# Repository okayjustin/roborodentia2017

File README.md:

# roborodentia2017

To rebuild the newlib libraries (embedded standard C libs):

	cd [REPOSITORY TOP LEVEL DIRECTORY]
	mkdir newlib_arm-none-eabi              					// Or whatever folder name you like
	cd newlib_arm-none-eabi
	../newlib-cygwin/configure
         --target=arm-none-eabi \
         --with-cpu=cortex-m4 \
         --with-fpu=fpv4-sp-d16 \
         --with-float=hard \
         --with-mode=thumb \
         --enable-interwork \        // Not sure if you need this one
         --enable-multilib \         // Not sure if you need this one
         --with-gnu-as \
         --with-gnu-ld \
         --disable-nls \
         --disable-newlib-supplied-syscalls  // Or whatever version of newlib source you have
    sudo make -j4 all

Then take the libc.a and libm.a from newlib_arm-none-eabi/arm-none-eabi/newlib and place them in buildTools.
Also take libnosys.a from newlib_arm-none-eabi/arm-none-eabi/thumb/libgloss/libnosys and place it in buildTools.

Then take the libc.a and libm.a from newlib_arm-none-eabi/arm-none-eabi/fpu/newlib and place them in buildTools.
Also take libnosys.a from newlib_arm-none-eabi/arm-none-eabi/fpu/libgloss/libnosys and place it in buildTools.

Debugging tips:

    > openocd -f firmware/buildTools/st_nucleo_f4.cfg
    > arm-none-eabi-gdb firmware/build/program.elf
    (gdb) target remote localhost:3333
    (gdb) monitor reset halt
    (gdb) b main.c:50
    (gdb) p data[0]
    (gdb) x/1hx 0x40005400

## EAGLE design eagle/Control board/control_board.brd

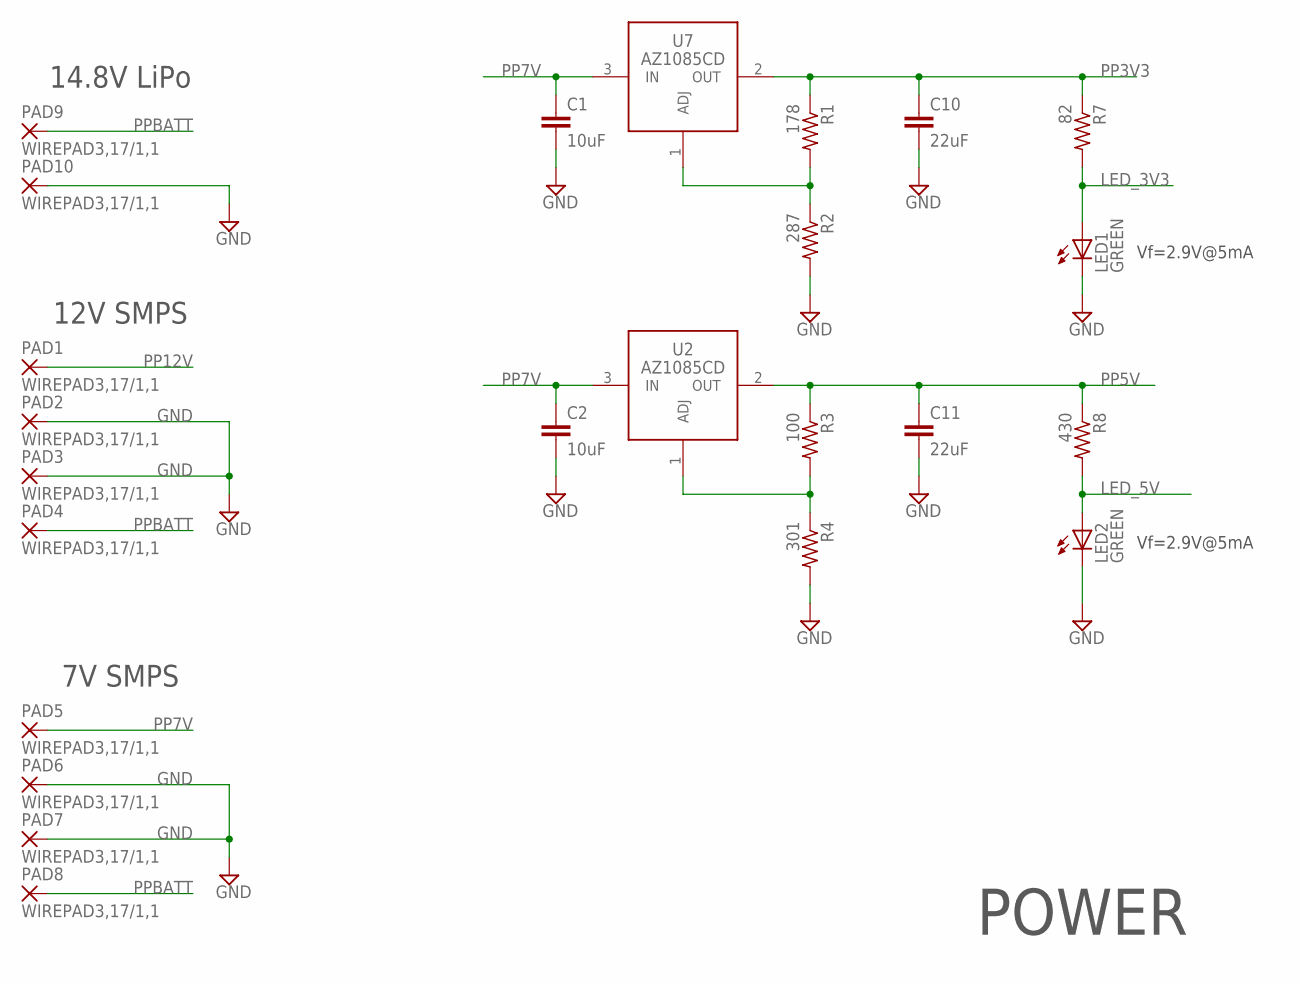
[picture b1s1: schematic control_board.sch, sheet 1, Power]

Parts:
C1, C2: 10uF; C0603
C10, C11: 22uF; C0603
LED1, LED2: GREEN; CHIPLED_0805; DIGI 732-4971-1-ND
PAD1, PAD2, PAD3, PAD4, PAD5, PAD6, PAD7, PAD8, PAD9, PAD10: WIREPAD3,17/1,1; 3,17/1,1
R1: 178; R0603
R2: 287; R0603
R3: 100; R0603
R4: 301; R0603
R7: 82; R0603
R8: 430; R0603
U2, U7: AZ1085CD; TO252

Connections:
GND: C1.2, C2.2, C10.2, C11.2, LED1.C, LED2.C, PAD2.1, PAD3.1, PAD6.1, PAD7.1, PAD10.1, R2.2, R4.2; also elsewhere on the board
LED_3V3: LED1.A, R7.2
LED_5V: LED2.A, R8.2
unnamed: R3.2, R4.1, U2.1 (ADJ)
unnamed: R1.2, R2.1, U7.1 (ADJ)
PP3V3: C10.1, R1.1, R7.1, U7.2 (OUT); also elsewhere on the board
PP5V: C11.1, R3.1, R8.1, U2.2 (OUT); also elsewhere on the board
PP7V: C1.1, C2.1, PAD5.1, U2.3 (IN), U7.3 (IN); also elsewhere on the board
PP12V: PAD1.1; also elsewhere on the board
PPBATT: PAD4.1, PAD8.1, PAD9.1

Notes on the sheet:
14.8V LiPo
12V SMPS
7V SMPS
Vf=2.9V@5mA
POWER

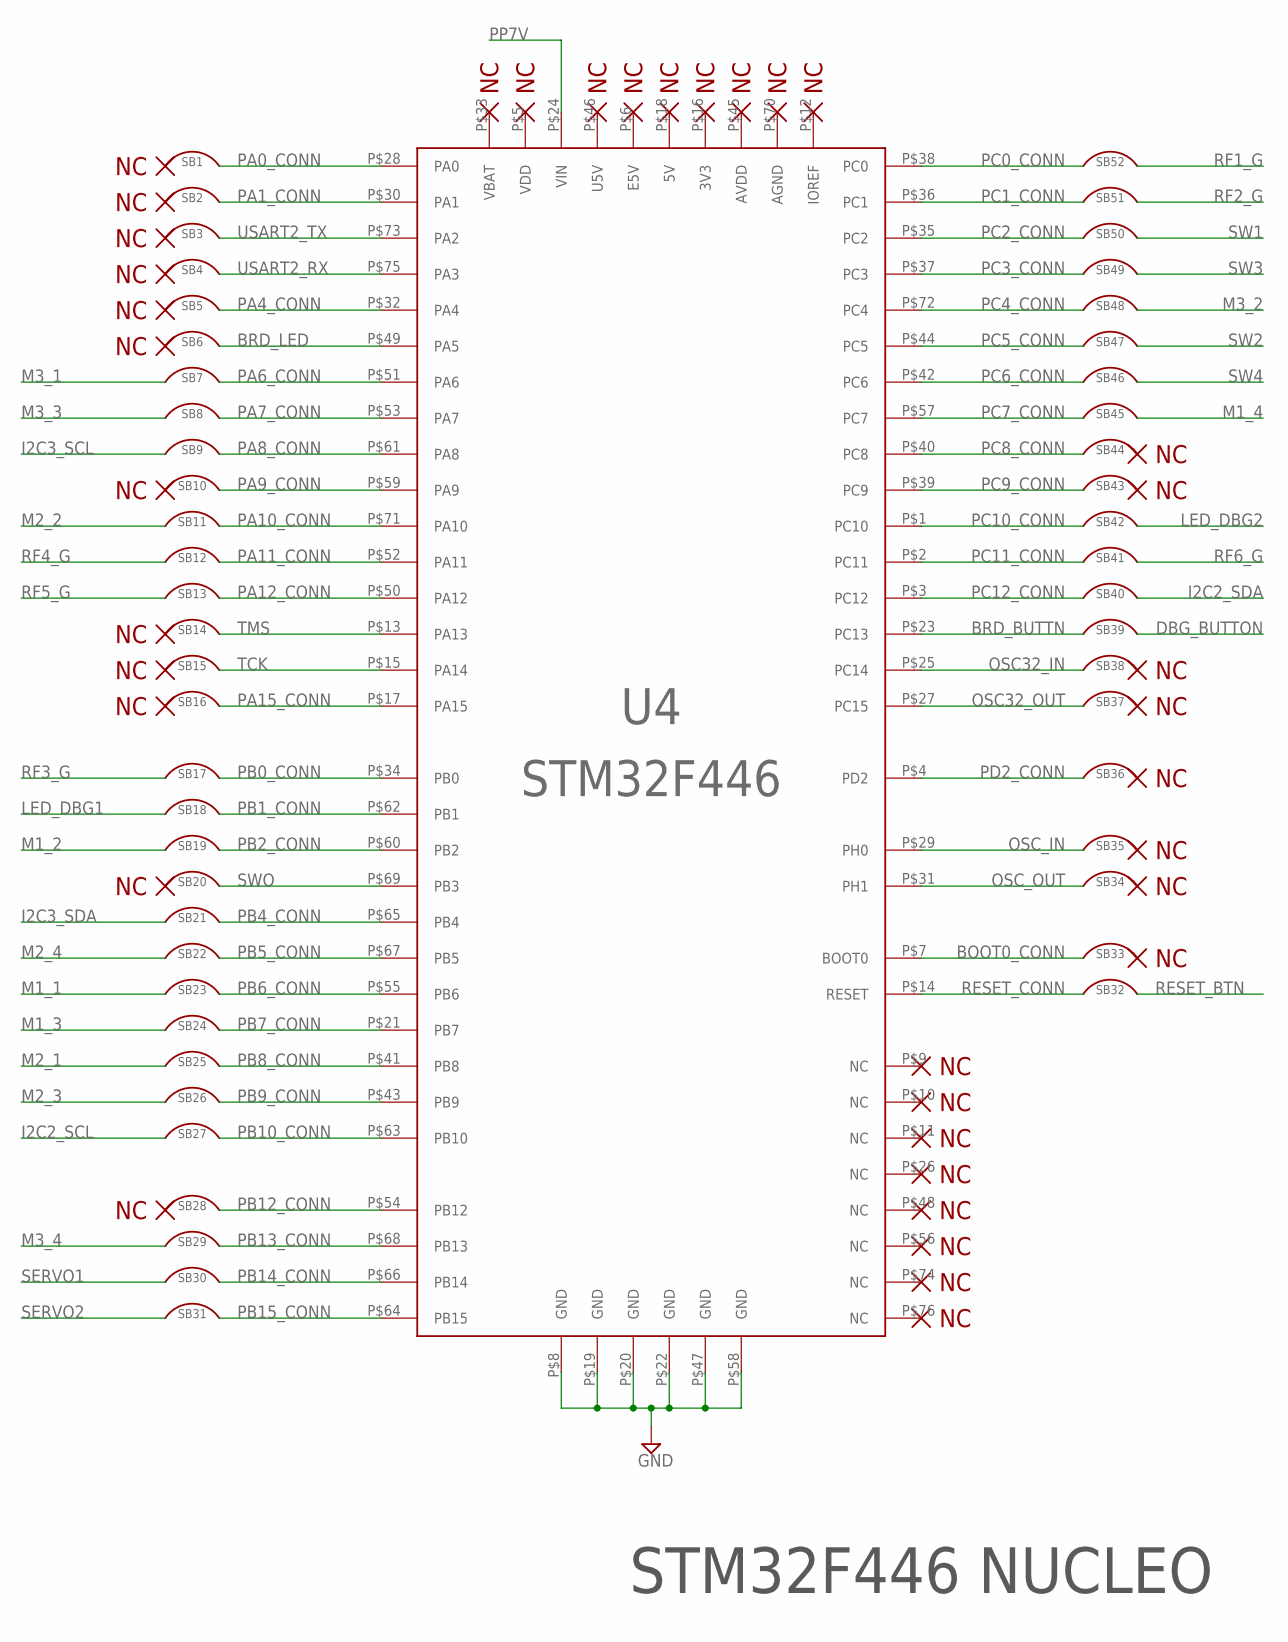
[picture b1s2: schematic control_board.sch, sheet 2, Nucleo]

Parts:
SB1, SB2, SB3, SB4, SB5, SB6, SB7, SB8, SB9, SB10, SB11, SB12, SB13, SB14, SB15, SB16, SB17, SB18, SB19, SB20, SB21, SB22, SB23, SB24, SB25, SB26, SB27, SB28, SB29, SB30, SB31, SB32, SB33, SB34, SB35, SB36, SB37, SB38, SB39, SB40, SB41, SB42, SB43, SB44, SB45, SB46, SB47, SB48, SB49, SB50, SB51, SB52: SOLDER_BRIDGE
U4: STM32F446; NUCLEO

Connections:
BOOT0_CONN: SB33.P$1, U4.P$7 (BOOT0)
BRD_BUTTN: SB39.P$1, U4.P$23 (PC13)
BRD_LED: SB6.P$2, U4.P$49 (PA5)
DBG_BUTTON: SB39.P$2; also elsewhere on the board
GND: U4.P$8 (GND), U4.P$19 (GND), U4.P$20 (GND), U4.P$22 (GND), U4.P$47 (GND), U4.P$58 (GND); also elsewhere on the board
I2C2_SCL: SB27.P$1; also elsewhere on the board
I2C2_SDA: SB40.P$2; also elsewhere on the board
I2C3_SCL: SB9.P$1; also elsewhere on the board
I2C3_SDA: SB21.P$1; also elsewhere on the board
LED_DBG1: SB18.P$1; also elsewhere on the board
LED_DBG2: SB42.P$2; also elsewhere on the board
M1_1: SB23.P$1; also elsewhere on the board
M1_2: SB19.P$1; also elsewhere on the board
M1_3: SB24.P$1; also elsewhere on the board
M1_4: SB45.P$1; also elsewhere on the board
M2_1: SB25.P$1; also elsewhere on the board
M2_2: SB11.P$1; also elsewhere on the board
M2_3: SB26.P$1; also elsewhere on the board
M2_4: SB22.P$1; also elsewhere on the board
M3_1: SB7.P$1; also elsewhere on the board
M3_2: SB48.P$2; also elsewhere on the board
M3_3: SB8.P$1; also elsewhere on the board
M3_4: SB29.P$1; also elsewhere on the board
OSC32_IN: SB38.P$1, U4.P$25 (PC14)
OSC32_OUT: SB37.P$1, U4.P$27 (PC15)
OSC_IN: SB35.P$1, U4.P$29 (PH0)
OSC_OUT: SB34.P$1, U4.P$31 (PH1)
PA0_CONN: SB1.P$2, U4.P$28 (PA0)
PA1_CONN: SB2.P$2, U4.P$30 (PA1)
PA4_CONN: SB5.P$2, U4.P$32 (PA4)
PA6_CONN: SB7.P$2, U4.P$51 (PA6)
PA7_CONN: SB8.P$2, U4.P$53 (PA7)
PA8_CONN: SB9.P$2, U4.P$61 (PA8)
PA9_CONN: SB10.P$2, U4.P$59 (PA9)
PA10_CONN: SB11.P$2, U4.P$71 (PA10)
PA11_CONN: SB12.P$2, U4.P$52 (PA11)
PA12_CONN: SB13.P$2, U4.P$50 (PA12)
PA15_CONN: SB16.P$2, U4.P$17 (PA15)
PB0_CONN: SB17.P$2, U4.P$34 (PB0)
PB1_CONN: SB18.P$2, U4.P$62 (PB1)
PB2_CONN: SB19.P$2, U4.P$60 (PB2)
PB4_CONN: SB21.P$2, U4.P$65 (PB4)
PB5_CONN: SB22.P$2, U4.P$67 (PB5)
PB6_CONN: SB23.P$2, U4.P$55 (PB6)
PB7_CONN: SB24.P$2, U4.P$21 (PB7)
PB8_CONN: SB25.P$2, U4.P$41 (PB8)
PB9_CONN: SB26.P$2, U4.P$43 (PB9)
PB10_CONN: SB27.P$2, U4.P$63 (PB10)
PB12_CONN: SB28.P$2, U4.P$54 (PB12)
PB13_CONN: SB29.P$2, U4.P$68 (PB13)
PB14_CONN: SB30.P$2, U4.P$66 (PB14)
PB15_CONN: SB31.P$2, U4.P$64 (PB15)
PC0_CONN: SB52.P$2, U4.P$38 (PC0)
PC1_CONN: SB51.P$2, U4.P$36 (PC1)
PC2_CONN: SB50.P$1, U4.P$35 (PC2)
PC3_CONN: SB49.P$1, U4.P$37 (PC3)
PC4_CONN: SB48.P$1, U4.P$72 (PC4)
PC5_CONN: SB47.P$1, U4.P$44 (PC5)
PC6_CONN: SB46.P$1, U4.P$42 (PC6)
PC7_CONN: SB45.P$2, U4.P$57 (PC7)
PC8_CONN: SB44.P$1, U4.P$40 (PC8)
PC9_CONN: SB43.P$2, U4.P$39 (PC9)
PC10_CONN: SB42.P$1, U4.P$1 (PC10)
PC11_CONN: SB41.P$1, U4.P$2 (PC11)
PC12_CONN: SB40.P$1, U4.P$3 (PC12)
PD2_CONN: SB36.P$1, U4.P$4 (PD2)
PP7V: U4.P$24 (VIN); also elsewhere on the board
RESET_BTN: SB32.P$2; also elsewhere on the board
RESET_CONN: SB32.P$1, U4.P$14 (RESET)
RF1_G: SB52.P$1; also elsewhere on the board
RF2_G: SB51.P$1; also elsewhere on the board
RF3_G: SB17.P$1; also elsewhere on the board
RF4_G: SB12.P$1; also elsewhere on the board
RF5_G: SB13.P$1; also elsewhere on the board
RF6_G: SB41.P$2; also elsewhere on the board
SERVO1: SB30.P$1; also elsewhere on the board
SERVO2: SB31.P$1; also elsewhere on the board
SW1: SB50.P$2; also elsewhere on the board
SW2: SB47.P$2; also elsewhere on the board
SW3: SB49.P$2; also elsewhere on the board
SW4: SB46.P$2; also elsewhere on the board
SWO: SB20.P$2, U4.P$69 (PB3)
TCK: SB15.P$2, U4.P$15 (PA14)
TMS: SB14.P$2, U4.P$13 (PA13)
USART2_RX: SB4.P$2, U4.P$75 (PA3)
USART2_TX: SB3.P$2, U4.P$73 (PA2)

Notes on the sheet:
STM32F446 NUCLEO

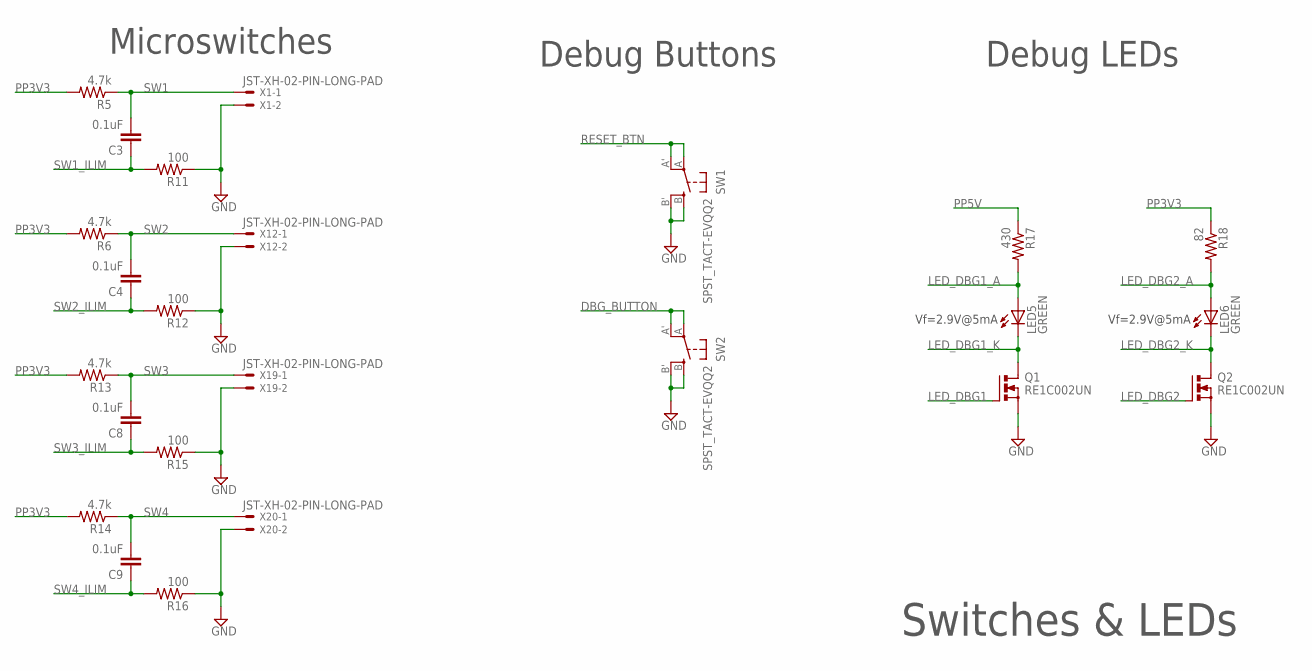
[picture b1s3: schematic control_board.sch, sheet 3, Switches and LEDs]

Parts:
C3, C4, C8, C9: 0.1uF; C0603
LED5, LED6: GREEN; CHIPLED_0805; DIGI 732-4971-1-ND
Q1, Q2: RE1C002UN; SOT416FL
R5, R6, R13, R14: 4.7k; R0603
R11, R12, R15, R16: 100; R0603
R17: 430; R0603
R18: 82; R0603
SW1, SW2: SPST_TACT-EVQQ2; EVQ-Q2; DIGI P12955SCT-ND
X1, X12, X19, X20: JST-XH-02-PIN-LONG-PAD; JST-XH-02-PACKAGE-LONG-PAD

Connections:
DBG_BUTTON: SW2.A, SW2.A' (P1); also elsewhere on the board
GND: Q1.P$2 (S), Q2.P$2 (S), R11.1, R12.1, R15.1, R16.1, SW1.B (S), SW1.B' (S1), SW2.B (S), SW2.B' (S1), X1.2, X12.2, X19.2, X20.2; also elsewhere on the board
LED_DBG1: Q1.P$1 (G); also elsewhere on the board
LED_DBG1_A: LED5.A, R17.2
LED_DBG1_K: LED5.C, Q1.P$3 (D)
LED_DBG2: Q2.P$1 (G); also elsewhere on the board
LED_DBG2_A: LED6.A, R18.2
LED_DBG2_K: LED6.C, Q2.P$3 (D)
PP3V3: R5.2, R6.2, R13.2, R14.2, R18.1; also elsewhere on the board
PP5V: R17.1; also elsewhere on the board
RESET_BTN: SW1.A, SW1.A' (P1); also elsewhere on the board
SW1: C3.2, R5.1, X1.1; also elsewhere on the board
SW1_ILIM: C3.1, R11.2
SW2: C4.2, R6.1, X12.1; also elsewhere on the board
SW2_ILIM: C4.1, R12.2
SW3: C8.2, R13.1, X19.1; also elsewhere on the board
SW3_ILIM: C8.1, R15.2
SW4: C9.2, R14.1, X20.1; also elsewhere on the board
SW4_ILIM: C9.1, R16.2

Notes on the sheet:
Microswitches
Vf=2.9V@5mA
Debug LEDs
Debug Buttons
Switches & LEDs

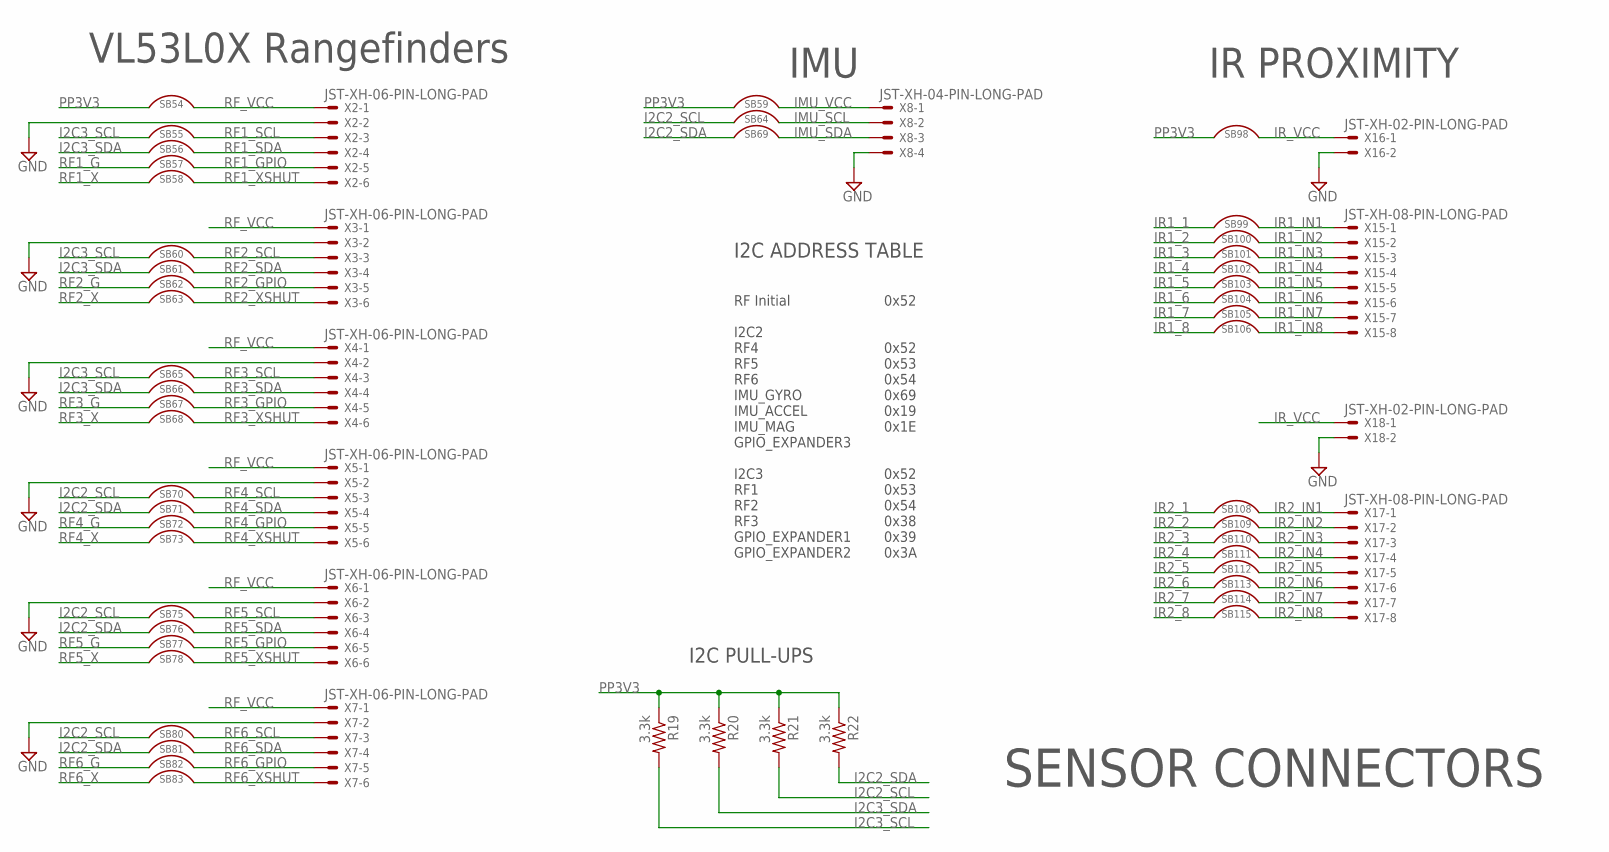
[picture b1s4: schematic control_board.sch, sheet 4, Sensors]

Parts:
R19, R20, R21, R22: 3.3k; R0603
SB54, SB55, SB56, SB57, SB58, SB59, SB60, SB61, SB62, SB63, SB64, SB65, SB66, SB67, SB68, SB69, SB70, SB71, SB72, SB73, SB75, SB76, SB77, SB78, SB80, SB81, SB82, SB83, SB98, SB99, SB100, SB101, SB102, SB103, SB104, SB105, SB106, SB108, SB109, SB110, SB111, SB112, SB113, SB114, SB115: SOLDER_BRIDGE
X2, X3, X4, X5, X6, X7: JST-XH-06-PIN-LONG-PAD; JST-XH-06-PACKAGE-LONG-PAD
X8: JST-XH-04-PIN-LONG-PAD; JST-XH-04-PACKAGE-LONG-PAD
X15, X17: JST-XH-08-PIN-LONG-PAD; JST-XH-08-PACKAGE-LONG-PAD
X16, X18: JST-XH-02-PIN-LONG-PAD; JST-XH-02-PACKAGE-LONG-PAD

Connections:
GND: X2.2, X3.2, X4.2, X5.2, X6.2, X7.2, X8.4, X16.2, X18.2; also elsewhere on the board
I2C2_SCL: R21.2, SB64.P$1, SB70.P$1, SB75.P$1, SB80.P$1; also elsewhere on the board
I2C2_SDA: R22.2, SB69.P$1, SB71.P$1, SB76.P$1, SB81.P$1; also elsewhere on the board
I2C3_SCL: R19.2, SB55.P$1, SB60.P$1, SB65.P$1; also elsewhere on the board
I2C3_SDA: R20.2, SB56.P$1, SB61.P$1, SB66.P$1; also elsewhere on the board
IMU_SCL: SB64.P$2, X8.2
IMU_SDA: SB69.P$2, X8.3
IMU_VCC: SB59.P$2, X8.1
IR1_1: SB99.P$1; also elsewhere on the board
IR1_2: SB100.P$1; also elsewhere on the board
IR1_3: SB101.P$1; also elsewhere on the board
IR1_4: SB102.P$1; also elsewhere on the board
IR1_5: SB103.P$1; also elsewhere on the board
IR1_6: SB104.P$1; also elsewhere on the board
IR1_7: SB105.P$1; also elsewhere on the board
IR1_8: SB106.P$1; also elsewhere on the board
IR1_IN1: SB99.P$2, X15.1
IR1_IN2: SB100.P$2, X15.2
IR1_IN3: SB101.P$2, X15.3
IR1_IN4: SB102.P$2, X15.4
IR1_IN5: SB103.P$2, X15.5
IR1_IN6: SB104.P$2, X15.6
IR1_IN7: SB105.P$2, X15.7
IR1_IN8: SB106.P$2, X15.8
IR2_1: SB108.P$1; also elsewhere on the board
IR2_2: SB109.P$1; also elsewhere on the board
IR2_3: SB110.P$1; also elsewhere on the board
IR2_4: SB111.P$1; also elsewhere on the board
IR2_5: SB112.P$1; also elsewhere on the board
IR2_6: SB113.P$1; also elsewhere on the board
IR2_7: SB114.P$1; also elsewhere on the board
IR2_8: SB115.P$1; also elsewhere on the board
IR2_IN1: SB108.P$2, X17.1
IR2_IN2: SB109.P$2, X17.2
IR2_IN3: SB110.P$2, X17.3
IR2_IN4: SB111.P$2, X17.4
IR2_IN5: SB112.P$2, X17.5
IR2_IN6: SB113.P$2, X17.6
IR2_IN7: SB114.P$2, X17.7
IR2_IN8: SB115.P$2, X17.8
IR_VCC: SB98.P$2, X16.1, X18.1
PP3V3: R19.1, R20.1, R21.1, R22.1, SB54.P$1, SB59.P$1, SB98.P$1; also elsewhere on the board
RF1_G: SB57.P$1; also elsewhere on the board
RF1_GPIO: SB57.P$2, X2.5
RF1_SCL: SB55.P$2, X2.3
RF1_SDA: SB56.P$2, X2.4
RF1_X: SB58.P$1; also elsewhere on the board
RF1_XSHUT: SB58.P$2, X2.6
RF2_G: SB62.P$1; also elsewhere on the board
RF2_GPIO: SB62.P$2, X3.5
RF2_SCL: SB60.P$2, X3.3
RF2_SDA: SB61.P$2, X3.4
RF2_X: SB63.P$1; also elsewhere on the board
RF2_XSHUT: SB63.P$2, X3.6
RF3_G: SB67.P$1; also elsewhere on the board
RF3_GPIO: SB67.P$2, X4.5
RF3_SCL: SB65.P$2, X4.3
RF3_SDA: SB66.P$2, X4.4
RF3_X: SB68.P$1; also elsewhere on the board
RF3_XSHUT: SB68.P$2, X4.6
RF4_G: SB72.P$1; also elsewhere on the board
RF4_GPIO: SB72.P$2, X5.5
RF4_SCL: SB70.P$2, X5.3
RF4_SDA: SB71.P$2, X5.4
RF4_X: SB73.P$1; also elsewhere on the board
RF4_XSHUT: SB73.P$2, X5.6
RF5_G: SB77.P$1; also elsewhere on the board
RF5_GPIO: SB77.P$2, X6.5
RF5_SCL: SB75.P$2, X6.3
RF5_SDA: SB76.P$2, X6.4
RF5_X: SB78.P$1; also elsewhere on the board
RF5_XSHUT: SB78.P$2, X6.6
RF6_G: SB82.P$1; also elsewhere on the board
RF6_GPIO: SB82.P$2, X7.5
RF6_SCL: SB80.P$2, X7.3
RF6_SDA: SB81.P$2, X7.4
RF6_X: SB83.P$1; also elsewhere on the board
RF6_XSHUT: SB83.P$2, X7.6
RF_VCC: SB54.P$2, X2.1, X3.1, X4.1, X5.1, X6.1, X7.1

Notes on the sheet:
VL53L0X Rangefinders
IMU
IR PROXIMITY
I2C ADDRESS TABLE
SENSOR CONNECTORS
RF Initial I2C2 RF4 RF5 RF6 IMU_GYRO IMU_ACCEL IMU_MAG GPIO_EXPANDER3 I2C3 RF1 RF2 RF3 GPIO_EXPANDER1 GPIO_EXPANDER2
0x52 0x52 0x53 0x54 0x69 0x19 0x1E 0x52 0x53 0x54 0x38 0x39 0x3A
I2C PULL-UPS

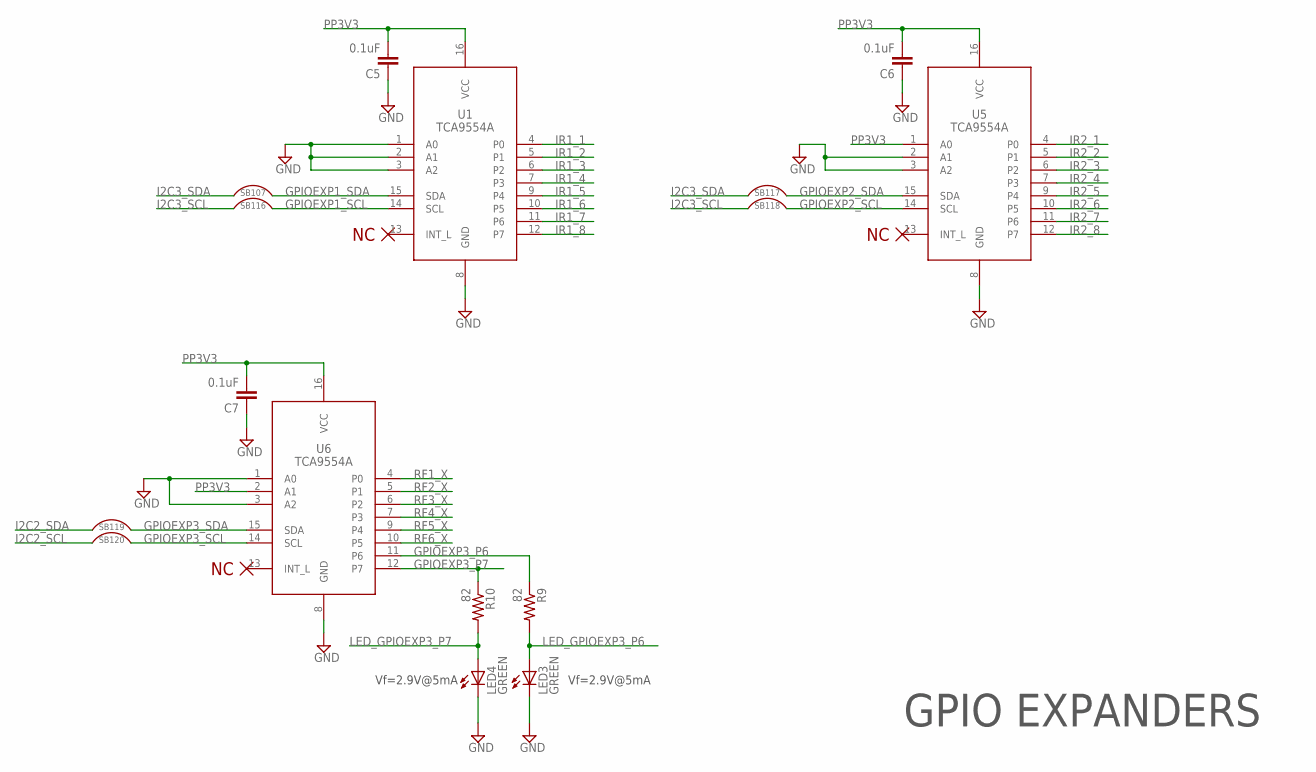
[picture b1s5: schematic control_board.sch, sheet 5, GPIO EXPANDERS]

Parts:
C5, C6, C7: 0.1uF; C0603
LED3, LED4: GREEN; CHIPLED_0805; DIGI 732-4971-1-ND
R9, R10: 82; R0603
SB107, SB116, SB117, SB118, SB119, SB120: SOLDER_BRIDGE
U1, U5, U6: TCA9554A; SOIC16-1.27-10.2X7.5MM

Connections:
GND: C5.1, C6.1, C7.1, LED3.C, LED4.C, U1.1 (A0), U1.2 (A1), U1.3 (A2), U1.8 (GND), U5.2 (A1), U5.3 (A2), U5.8 (GND), U6.1 (A0), U6.3 (A2), U6.8 (GND); also elsewhere on the board
GPIOEXP1_SCL: SB116.P$2, U1.14 (SCL)
GPIOEXP1_SDA: SB107.P$2, U1.15 (SDA)
GPIOEXP2_SCL: SB118.P$2, U5.14 (SCL)
GPIOEXP2_SDA: SB117.P$2, U5.15 (SDA)
GPIOEXP3_P6: R9.1, U6.11 (P6)
GPIOEXP3_P7: R10.1, U6.12 (P7)
GPIOEXP3_SCL: SB120.P$2, U6.14 (SCL)
GPIOEXP3_SDA: SB119.P$2, U6.15 (SDA)
I2C2_SCL: SB120.P$1; also elsewhere on the board
I2C2_SDA: SB119.P$1; also elsewhere on the board
I2C3_SCL: SB116.P$1, SB118.P$1; also elsewhere on the board
I2C3_SDA: SB107.P$1, SB117.P$1; also elsewhere on the board
IR1_1: U1.4 (P0); also elsewhere on the board
IR1_2: U1.5 (P1); also elsewhere on the board
IR1_3: U1.6 (P2); also elsewhere on the board
IR1_4: U1.7 (P3); also elsewhere on the board
IR1_5: U1.9 (P4); also elsewhere on the board
IR1_6: U1.10 (P5); also elsewhere on the board
IR1_7: U1.11 (P6); also elsewhere on the board
IR1_8: U1.12 (P7); also elsewhere on the board
IR2_1: U5.4 (P0); also elsewhere on the board
IR2_2: U5.5 (P1); also elsewhere on the board
IR2_3: U5.6 (P2); also elsewhere on the board
IR2_4: U5.7 (P3); also elsewhere on the board
IR2_5: U5.9 (P4); also elsewhere on the board
IR2_6: U5.10 (P5); also elsewhere on the board
IR2_7: U5.11 (P6); also elsewhere on the board
IR2_8: U5.12 (P7); also elsewhere on the board
LED_GPIOEXP3_P6: LED3.A, R9.2
LED_GPIOEXP3_P7: LED4.A, R10.2
PP3V3: C5.2, C6.2, C7.2, U1.16 (VCC), U5.1 (A0), U5.16 (VCC), U6.2 (A1), U6.16 (VCC); also elsewhere on the board
RF1_X: U6.4 (P0); also elsewhere on the board
RF2_X: U6.5 (P1); also elsewhere on the board
RF3_X: U6.6 (P2); also elsewhere on the board
RF4_X: U6.7 (P3); also elsewhere on the board
RF5_X: U6.9 (P4); also elsewhere on the board
RF6_X: U6.10 (P5); also elsewhere on the board

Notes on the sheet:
GPIO EXPANDERS
Vf=2.9V@5mA

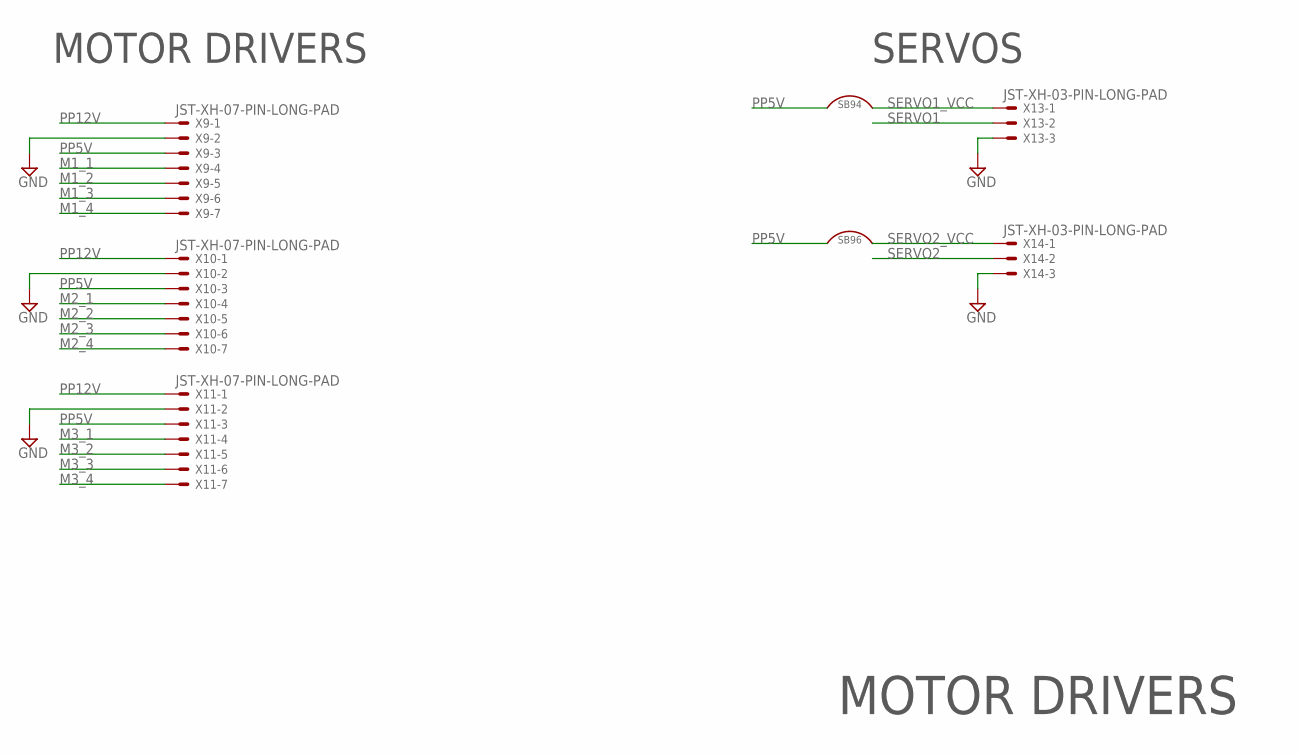
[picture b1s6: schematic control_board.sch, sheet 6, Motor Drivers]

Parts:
SB94, SB96: SOLDER_BRIDGE
X9, X10, X11: JST-XH-07-PIN-LONG-PAD; JST-XH-07-PACKAGE-LONG-PAD
X13, X14: JST-XH-03-PIN-LONG-PAD; JST-XH-03-PACKAGE-LONG-PAD

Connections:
GND: X9.2, X10.2, X11.2, X13.3, X14.3; also elsewhere on the board
M1_1: X9.4; also elsewhere on the board
M1_2: X9.5; also elsewhere on the board
M1_3: X9.6; also elsewhere on the board
M1_4: X9.7; also elsewhere on the board
M2_1: X10.4; also elsewhere on the board
M2_2: X10.5; also elsewhere on the board
M2_3: X10.6; also elsewhere on the board
M2_4: X10.7; also elsewhere on the board
M3_1: X11.4; also elsewhere on the board
M3_2: X11.5; also elsewhere on the board
M3_3: X11.6; also elsewhere on the board
M3_4: X11.7; also elsewhere on the board
PP5V: SB94.P$1, SB96.P$1, X9.3, X10.3, X11.3; also elsewhere on the board
PP12V: X9.1, X10.1, X11.1; also elsewhere on the board
SERVO1: X13.2; also elsewhere on the board
SERVO1_VCC: SB94.P$2, X13.1
SERVO2: X14.2; also elsewhere on the board
SERVO2_VCC: SB96.P$2, X14.1

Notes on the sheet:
MOTOR DRIVERS
SERVOS

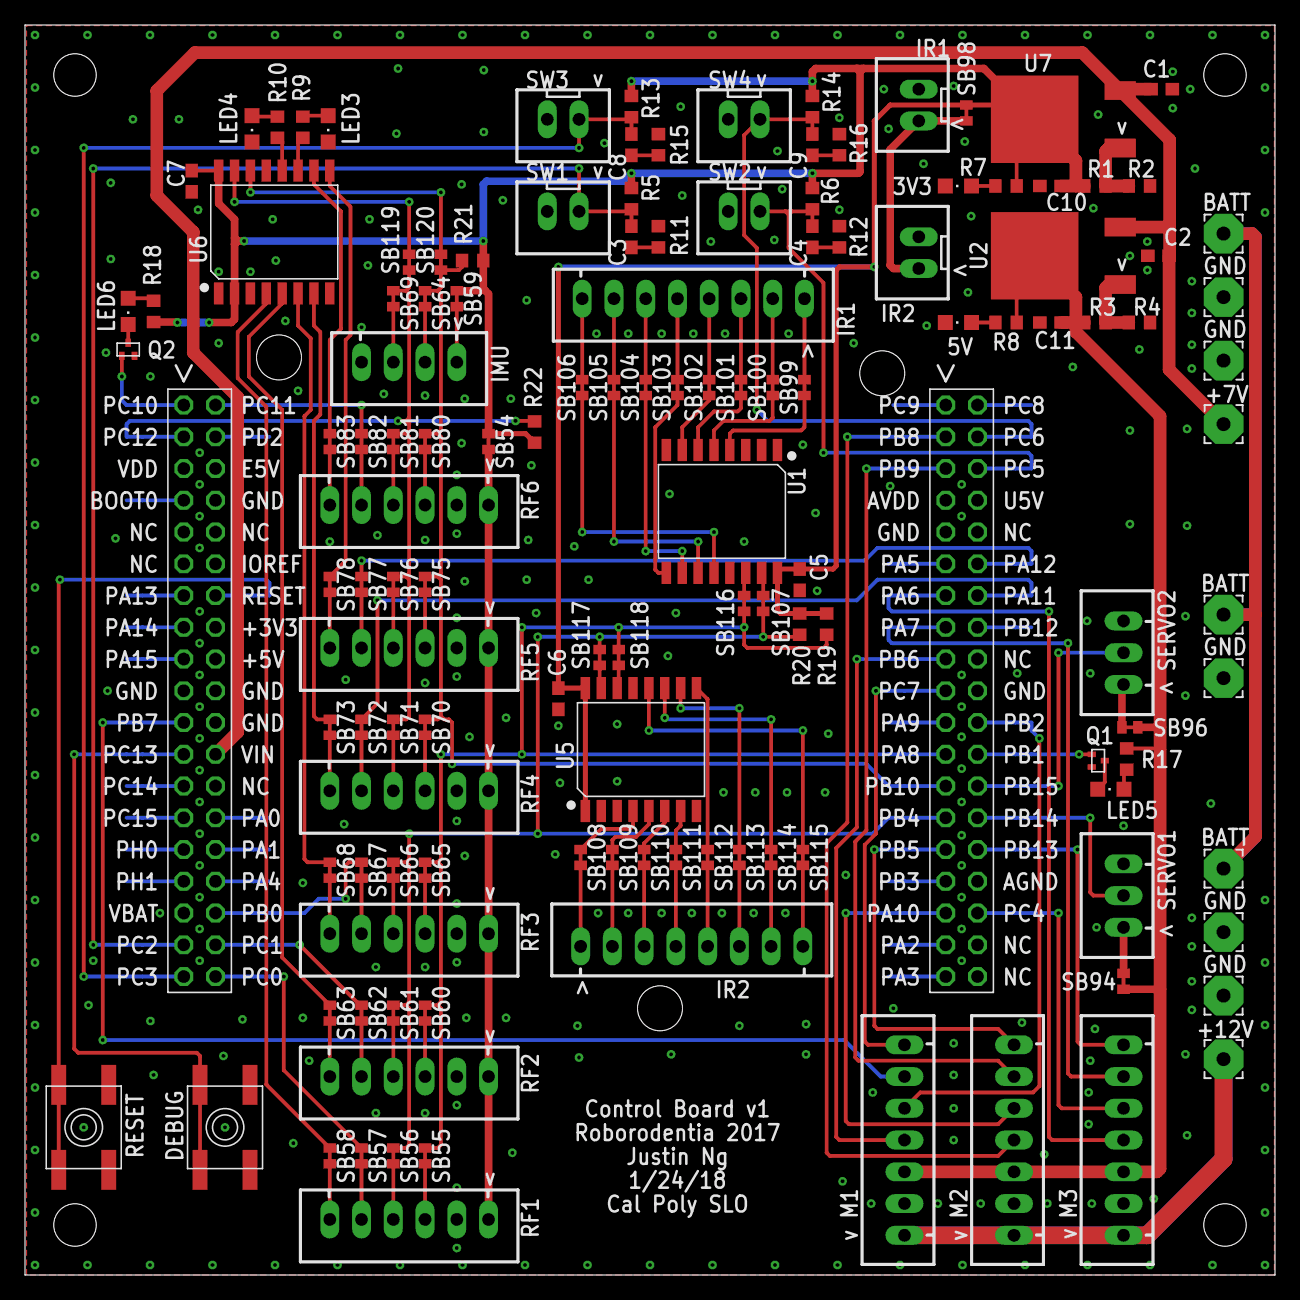
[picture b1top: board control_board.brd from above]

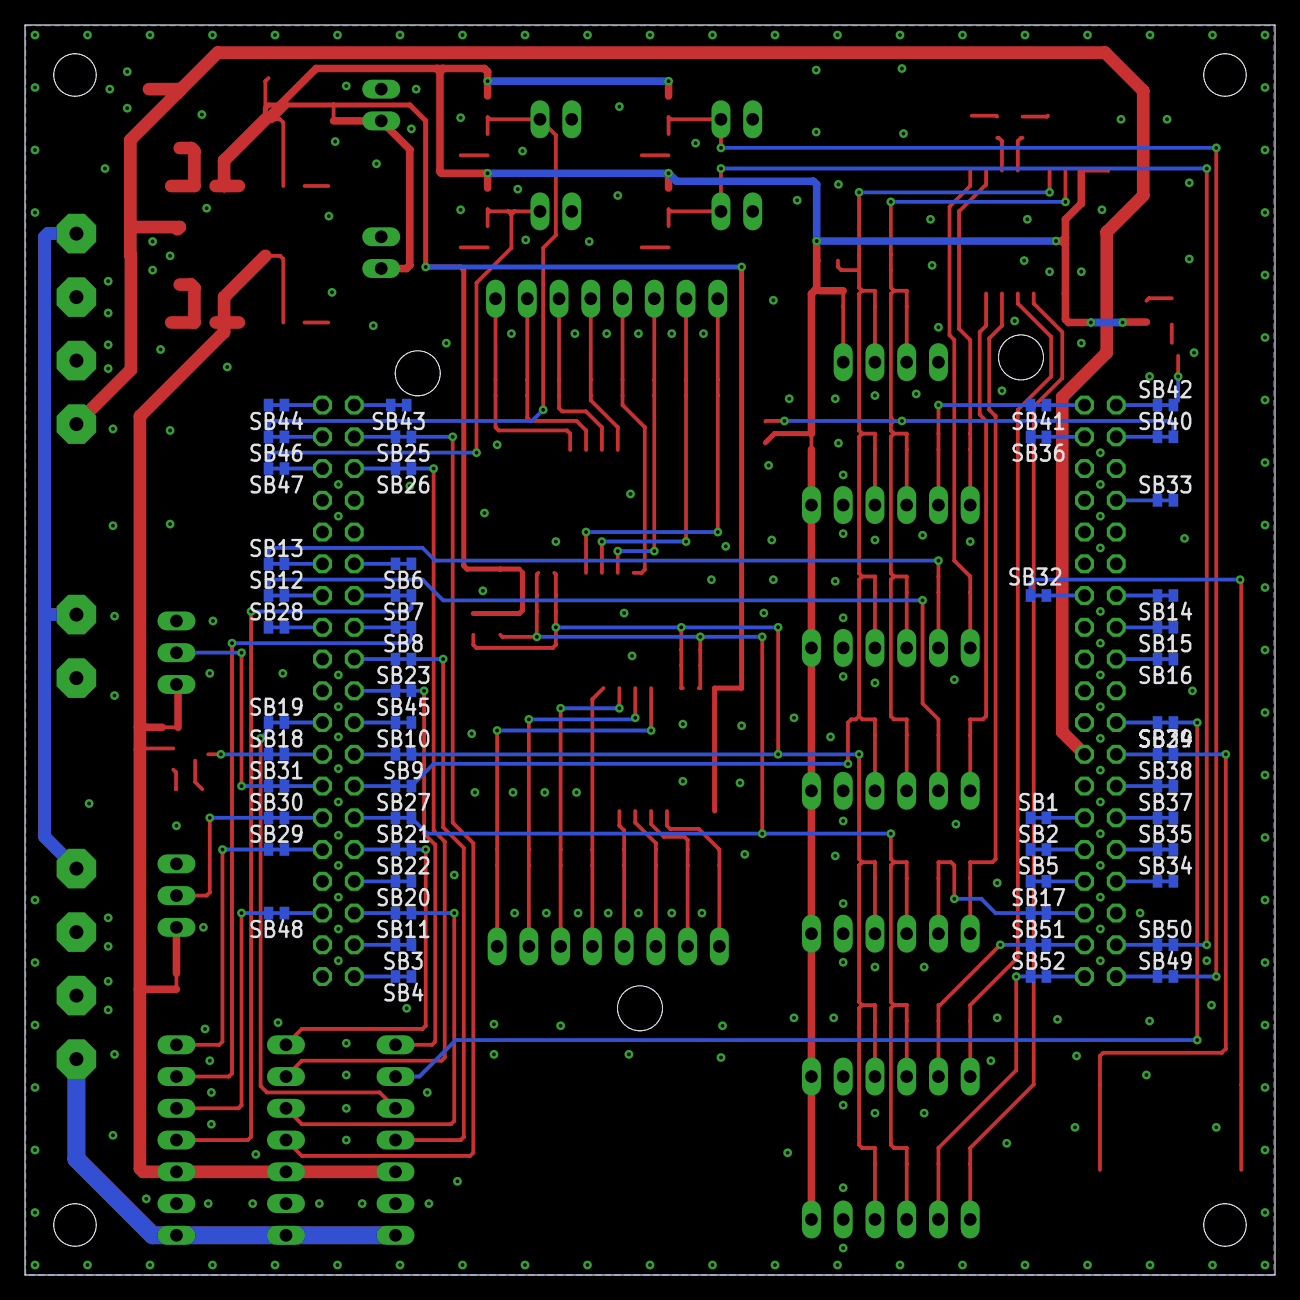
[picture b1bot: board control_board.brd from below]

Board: 2 copper layers, 100.0 x 100.0 mm, 184 parts (52 on the bottom side), 181 nets.

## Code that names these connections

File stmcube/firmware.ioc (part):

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Mcu.Name=STM32F446R(C-E)Tx
Mcu.Package=LQFP64
Mcu.UserName=STM32F446RETx
PA10.GPIOParameters=GPIO_Label
PA10.GPIO_Label=M2_2
PA10.Signal=GPIO_Output
PA11.GPIOParameters=GPIO_Label
PA11.GPIO_Label=RF4_G
PA11.Signal=GPIO_Output
PA12.GPIOParameters=GPIO_Label
PA12.GPIO_Label=RF5_G
PA12.Signal=GPIO_Output
PA13.GPIOParameters=GPIO_Label
PA13.GPIO_Label=TMS
PA13.Signal=SYS_JTMS-SWDIO
PA14.GPIOParameters=GPIO_Label
PA14.GPIO_Label=TCK
PA14.Signal=SYS_JTCK-SWCLK
PA2.GPIOParameters=GPIO_Label
PA2.GPIO_Label=USART_TX
PA2.Mode=Asynchronous
PA2.Signal=USART2_TX
PA3.GPIOParameters=GPIO_Label
PA3.GPIO_Label=USART_RX
PA3.Mode=Asynchronous
PA3.Signal=USART2_RX
PA5.GPIOParameters=GPIO_Label
PA5.GPIO_Label=LD2 [Green Led]
PA5.Signal=GPIO_Output
PA6.GPIOParameters=GPIO_Label
PA6.GPIO_Label=M3_1
PA6.Signal=S_TIM3_CH1
PA7.GPIOParameters=GPIO_Label
PA7.GPIO_Label=M3_3
PA7.Signal=S_TIM3_CH2
PA8.Mode=I2C
PA8.Signal=I2C3_SCL
PB0.GPIOParameters=GPIO_Label
PB0.GPIO_Label=RF3_G
PB0.Signal=GPIO_Output
PB1.GPIOParameters=GPIO_Label
PB1.GPIO_Label=LED_DBG1
PB1.Signal=GPIO_Output
PB10.Mode=I2C
PB10.Signal=I2C2_SCL
PB13.GPIOParameters=GPIO_Label
PB13.GPIO_Label=M3_4
PB13.Signal=GPIO_Output
PB14.GPIOParameters=GPIO_Label
PB14.GPIO_Label=SERVO1
PB14.Signal=S_TIM12_CH1
PB15.GPIOParameters=GPIO_Label
PB15.GPIO_Label=SERVO2
PB15.Signal=S_TIM12_CH2
PB2.GPIOParameters=GPIO_Label
PB2.GPIO_Label=M1_2
PB2.Signal=GPIO_Output
PB3.GPIOParameters=GPIO_Label
PB3.GPIO_Label=SWO
PB3.Signal=SYS_JTDO-SWO
PB4.Mode=I2C
PB4.Signal=I2C3_SDA
PB5.GPIOParameters=GPIO_Label
PB5.GPIO_Label=M2_4
PB5.Signal=GPIO_Output
PB6.GPIOParameters=GPIO_Label
PB6.GPIO_Label=M1_1
PB6.Signal=S_TIM4_CH1
PB7.GPIOParameters=GPIO_Label
PB7.GPIO_Label=M1_3
PB7.Signal=S_TIM4_CH2
PB8.GPIOParameters=GPIO_Label
PB8.GPIO_Label=M2_1
PB8.Signal=S_TIM4_CH3
PB9.GPIOParameters=GPIO_Label
PB9.GPIO_Label=M2_3
PB9.Signal=S_TIM4_CH4
PC0.GPIOParameters=GPIO_Label
PC0.GPIO_Label=RF1_G
PC0.Signal=GPIO_Output
PC1.GPIOParameters=GPIO_Label
PC1.GPIO_Label=RF2_G
PC1.Signal=GPIO_Output
PC10.GPIOParameters=GPIO_Label
PC10.GPIO_Label=LED_DBG2
PC10.Signal=GPIO_Output
PC11.GPIOParameters=GPIO_Label
PC11.GPIO_Label=RF6_G
PC11.Signal=GPIO_Output
PC12.Mode=I2C
PC12.Signal=I2C2_SDA
PC13.GPIOParameters=GPIO_Label,GPIO_ModeDefaultEXTI
PC13.GPIO_Label=B1 [Blue PushButton]
PC13.GPIO_ModeDefaultEXTI=GPIO_MODE_IT_FALLING
PC13.Signal=GPXTI13
PC14-OSC32_IN.Mode=LSE-External-Oscillator
PC14-OSC32_IN.Signal=RCC_OSC32_IN
PC15-OSC32_OUT.Mode=LSE-External-Oscillator
PC15-OSC32_OUT.Signal=RCC_OSC32_OUT
PC2.GPIOParameters=GPIO_Label
PC2.GPIO_Label=SW1
PC2.Signal=GPIO_Input
PC3.GPIOParameters=GPIO_Label
PC3.GPIO_Label=SW3
PC3.Signal=GPIO_Input
PC4.GPIOParameters=GPIO_Label
PC4.GPIO_Label=M3_2
PC4.Signal=GPIO_Output
PC5.GPIOParameters=GPIO_Label
PC5.GPIO_Label=SW2
PC5.Signal=GPIO_Input
PC6.GPIOParameters=GPIO_Label
PC6.GPIO_Label=SW4
PC6.Signal=GPIO_Input
PC7.GPIOParameters=GPIO_Label
PC7.GPIO_Label=M1_4
PC7.Signal=GPIO_Output
PH0-OSC_IN.Mode=HSE-External-Oscillator
PH0-OSC_IN.Signal=RCC_OSC_IN
PH1-OSC_OUT.Mode=HSE-External-Oscillator
PH1-OSC_OUT.Signal=RCC_OSC_OUT
RCC.HSE_VALUE=8000000
RCC.SYSCLKFreq_VALUE=180000000
RCC.SYSCLKSource=RCC_SYSCLKSOURCE_PLLCLK
board=NUCLEO-F446RE
boardIOC=true
